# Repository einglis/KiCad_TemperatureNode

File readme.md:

# Temperature Hub

A little board with a few connections for one-wire DS temperature sensors.

Code is included for completeness only

## HW mods
After production, I discovered that A6 and A7 can't be used for digital IOs, so I bodge-wired them to D4 and D3, repectively.  This is reflected in the schematic and code but not the PCB or gerbers.

## Dependencies
* https://github.com/hulkco/Nano_33/tree/master
* rfm12b symbol from ...??

## Pictures

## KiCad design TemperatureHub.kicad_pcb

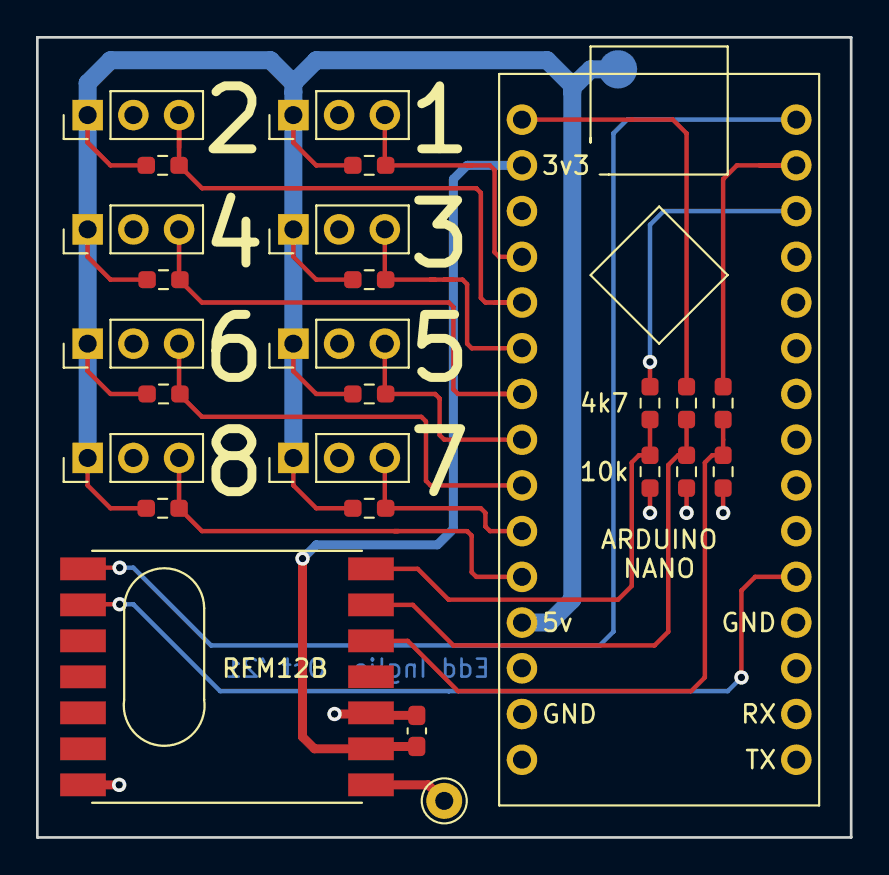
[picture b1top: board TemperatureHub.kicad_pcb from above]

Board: 2 copper layers, 45.2 x 44.4 mm, 26 parts (0 on the bottom side), 20 nets.

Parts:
C1: 0.1uF; C_0603_1608Metric_Pad1.08x0.95mm_HandSolder
J1: Arduino-NANO-33; NANO_33_Socket_Normal
J2, J4, J5, J6, J7, J8, J9, J10: Conn_01x03_Male; PinHeader_1x03_P2.54mm_Vertical
J3: Conn_01x01_Male; Pin_D1.0mm_L10.0mm
R1, R3, R5, R7, R8, R9, R10, R11, R12, R13, R14: 4k7; R_0603_1608Metric_Pad0.98x0.95mm_HandSolder
R2, R4, R6: 10k; R_0603_1608Metric_Pad0.98x0.95mm_HandSolder
U1: RFM12; rfm12b

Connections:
+3V3: C1.1, J1.2, U1.VDD
+5V: J1.12, J2.1, J4.1, J5.1, J6.1, J7.1, J8.1, J9.1, J10.1, R7.1, R8.1, R9.1, R10.1, R11.1, R12.2, R13.1, R14.1
/sensor0: J1.4, J4.3, R8.2
/sensor1: J1.5, J8.3, R12.1
/sensor2: J1.6, J2.3, R7.2
/sensor3: J1.7, J5.3, R9.2
/sensor4: J1.8, J6.3, R10.2
/sensor5: J1.9, J7.3, R11.2
/sensor6: J1.10, J9.3, R13.2
/sensor7: J1.11, J10.3, R14.2
GND: C1.2, J1.14, J1.19, J2.2, J4.2, J5.2, J6.2, J7.2, J8.2, J9.2, J10.2, R2.2, R4.2, R6.2, U1.GND
unnamed: J1.1, R1.2
unnamed: J1.20, U1.IRQ
unnamed: J1.28, R5.2
unnamed: J1.29, R3.2
unnamed: J1.30, U1.SDO
unnamed: J3.1, U1.ANT
unnamed: R1.1, R2.1, U1.SCK
unnamed: R3.1, R4.1, U1.SDI
unnamed: R5.1, R6.1, U1.SEL

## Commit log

2023-12-16 Restoring to working order, hopefully
2023-12-16 is committing a .zip of gerbers such a sin?!
2023-12-16 ignore another temporary file
2023-12-16 being a good citizen
2023-12-16 I think this was an old format that KiCad replace with kicad_sch
2023-12-16 moved the gerbers
2023-12-16 doc updates
2023-12-16 pictures
